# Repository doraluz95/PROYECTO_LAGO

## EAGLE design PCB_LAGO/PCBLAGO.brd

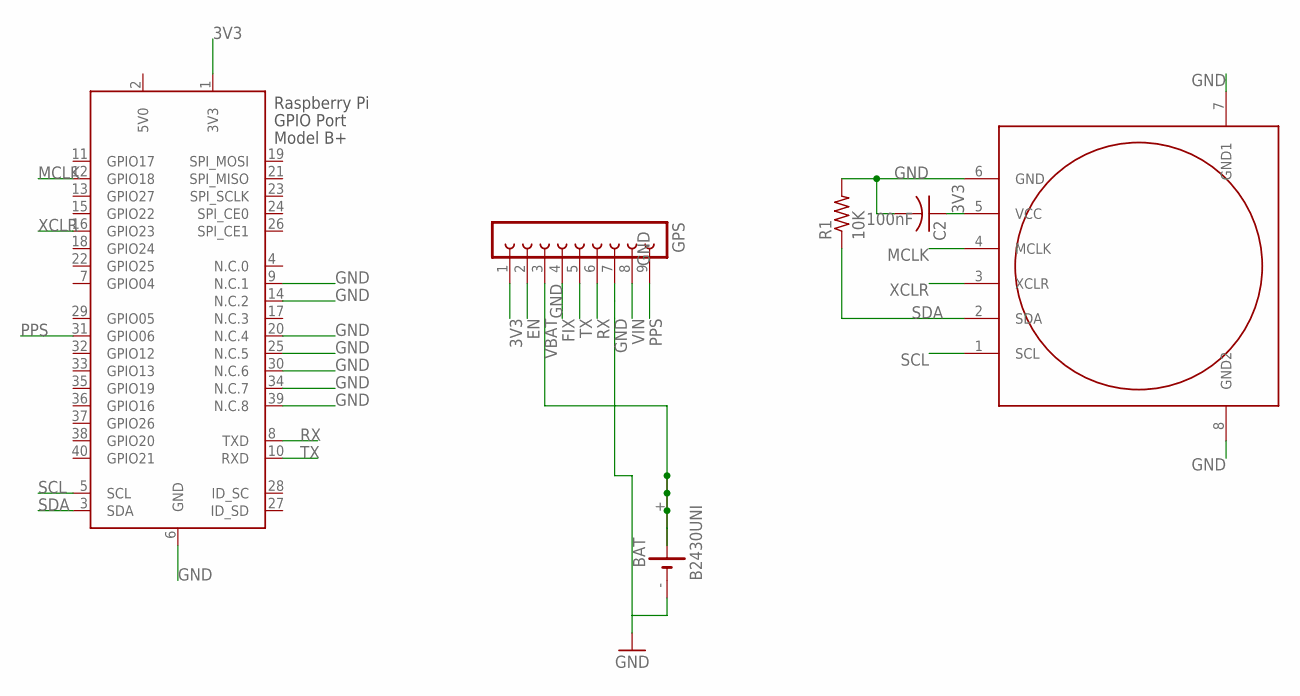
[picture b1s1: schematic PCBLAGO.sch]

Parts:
BAT: B2430UNI
C2: 100nF; C0805K
GPS: FE09-1; FE09
R1: 10K; M0805
U$1: HP03S
X1: RASPI_BOARD_B+_F; RASPI_BOARD_B+_FULL

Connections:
3V3: C2.1, GPS.1, U$1.5 (VCC), X1.1 (3V3)
5V0: X1.2 (5V0)
EN: GPS.2
FIX: GPS.4
GND: BAT.-, C2.2, GPS.7, R1.2, U$1.6 (GND), U$1.7 (GND1), U$1.8 (GND2), X1.6 (GND), X1.9 (N.C.1), X1.14 (N.C.2), X1.20 (N.C.4), X1.25 (N.C.5), X1.30 (N.C.6), X1.34 (N.C.7), X1.39 (N.C.8)
MCLK: U$1.4 (MCLK), X1.12 (GPIO18)
PPS: GPS.9, X1.31 (GPIO06)
RX: GPS.6, X1.8 (TXD)
SCL: U$1.1 (SCL), X1.5 (SCL)
SDA: R1.1, U$1.2 (SDA), X1.3 (SDA)
TX: GPS.5, X1.10 (RXD)
VBAT: BAT.+, BAT.+@1 (+), BAT.+@2 (+), BAT.+@3 (+), BAT.+@4 (+), GPS.3
VIN: GPS.8
XCLR: U$1.3 (XCLR), X1.16 (GPIO23)

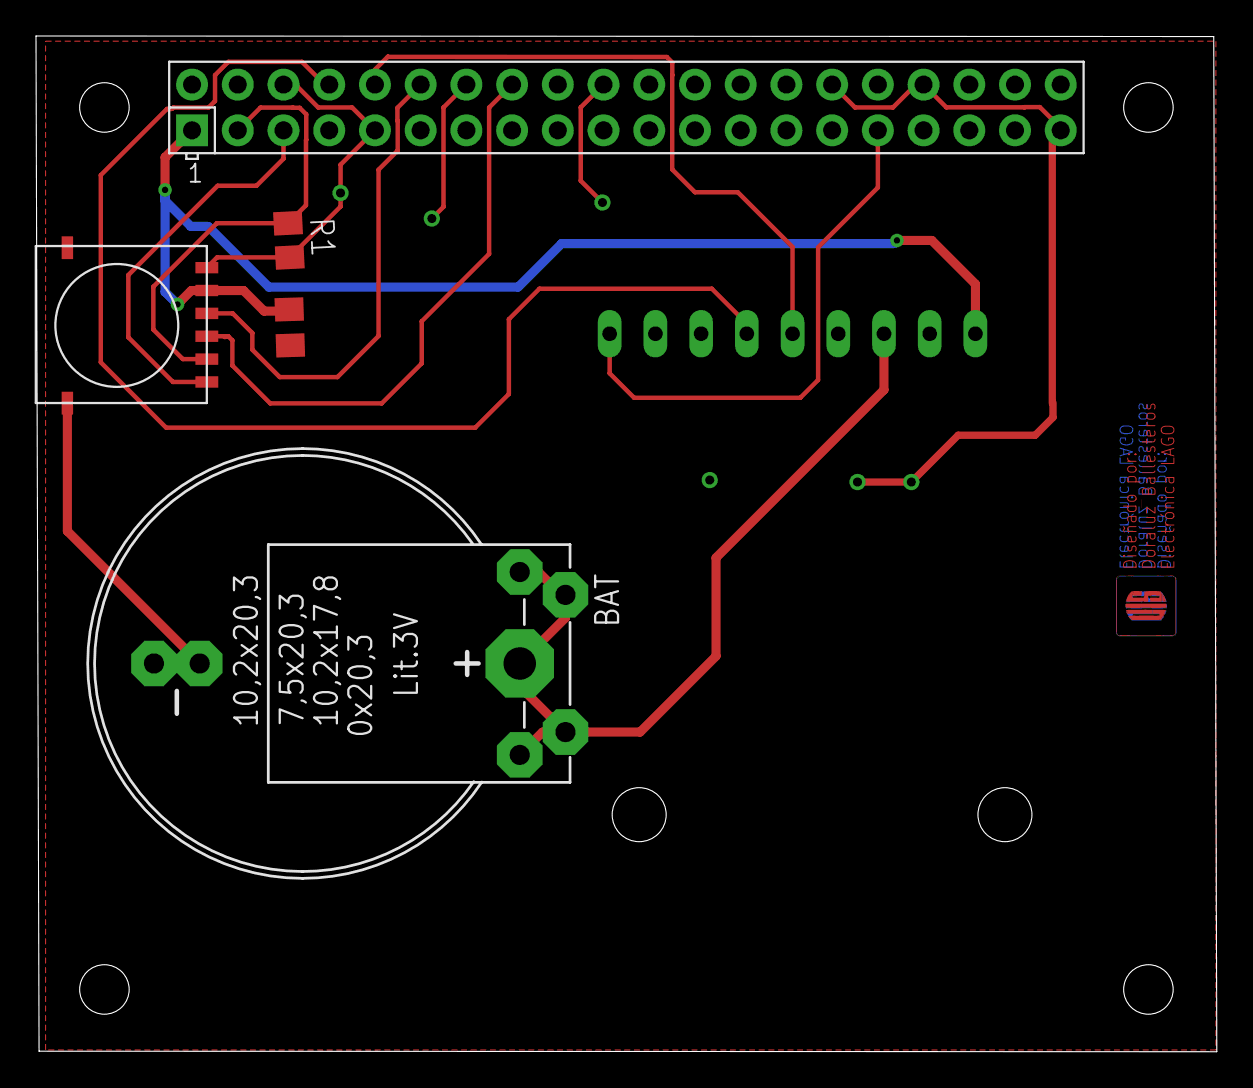
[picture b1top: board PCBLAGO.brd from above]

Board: 2 copper layers, 65.6 x 56.4 mm, 6 parts (1 on the bottom side), 10 nets.

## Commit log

2020-05-04 Initial Overleaf Import
2020-05-04 Create PCB_LAGO
2020-05-04 PCB_LAGO
2020-05-05 Create CODIGOS_VERILOG
2020-05-07 presentacion
2020-05-08 version 1
2020-05-08 libro lago
2020-05-08 proyecto lago
2020-05-20 add makefile for generate raspberry bitstream
2020-05-20 add gitignore
2020-05-20 add readme for python libreries, add hp03s compiled program
2020-05-21 update constrains
